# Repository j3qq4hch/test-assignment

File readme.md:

# SFP module

This repository contains source documentation for Gigabit SFP module based on RTL8211FS.
This is some sort of test assignment and not a real device.
The design is not tested in hardware (though looks fine in theory).

The design was done in EagleCAD. Any version starting from 7.7 should open the design just fine. 
3D model generated using NoABS.Eagle3d tool (not released yet).

The device looks like this:

3d model of the device is available [here](https://j3qq4hch.github.io/test-assignment/index.html?model=sfp.glb).

Schematic in pdf format can be found [here](sch.pdf).

One of the requirements of this test assignment was to find flaws in the design and fix them. Below is a list of these flaws:

* The overall schematic quality is poor.
* TXD+/TXD- on SFP connector side must be swapped.
* Ethernet connector has no embedded magnetics. Had to replace connector with [HanRun HR911130C](https://www.chipdip.ru/product/hr911130c-razyomy-i-soediniteli-hanrun-8048835943).
* The PCB is too narrow for the ethernet connector. It has to be a bit wider. 
* Some of the decoupling capacitors missing.
* Using proprietary and very expensive software for a test assignment likely assumes that the candidate will use pirated software, which is not a good practice.

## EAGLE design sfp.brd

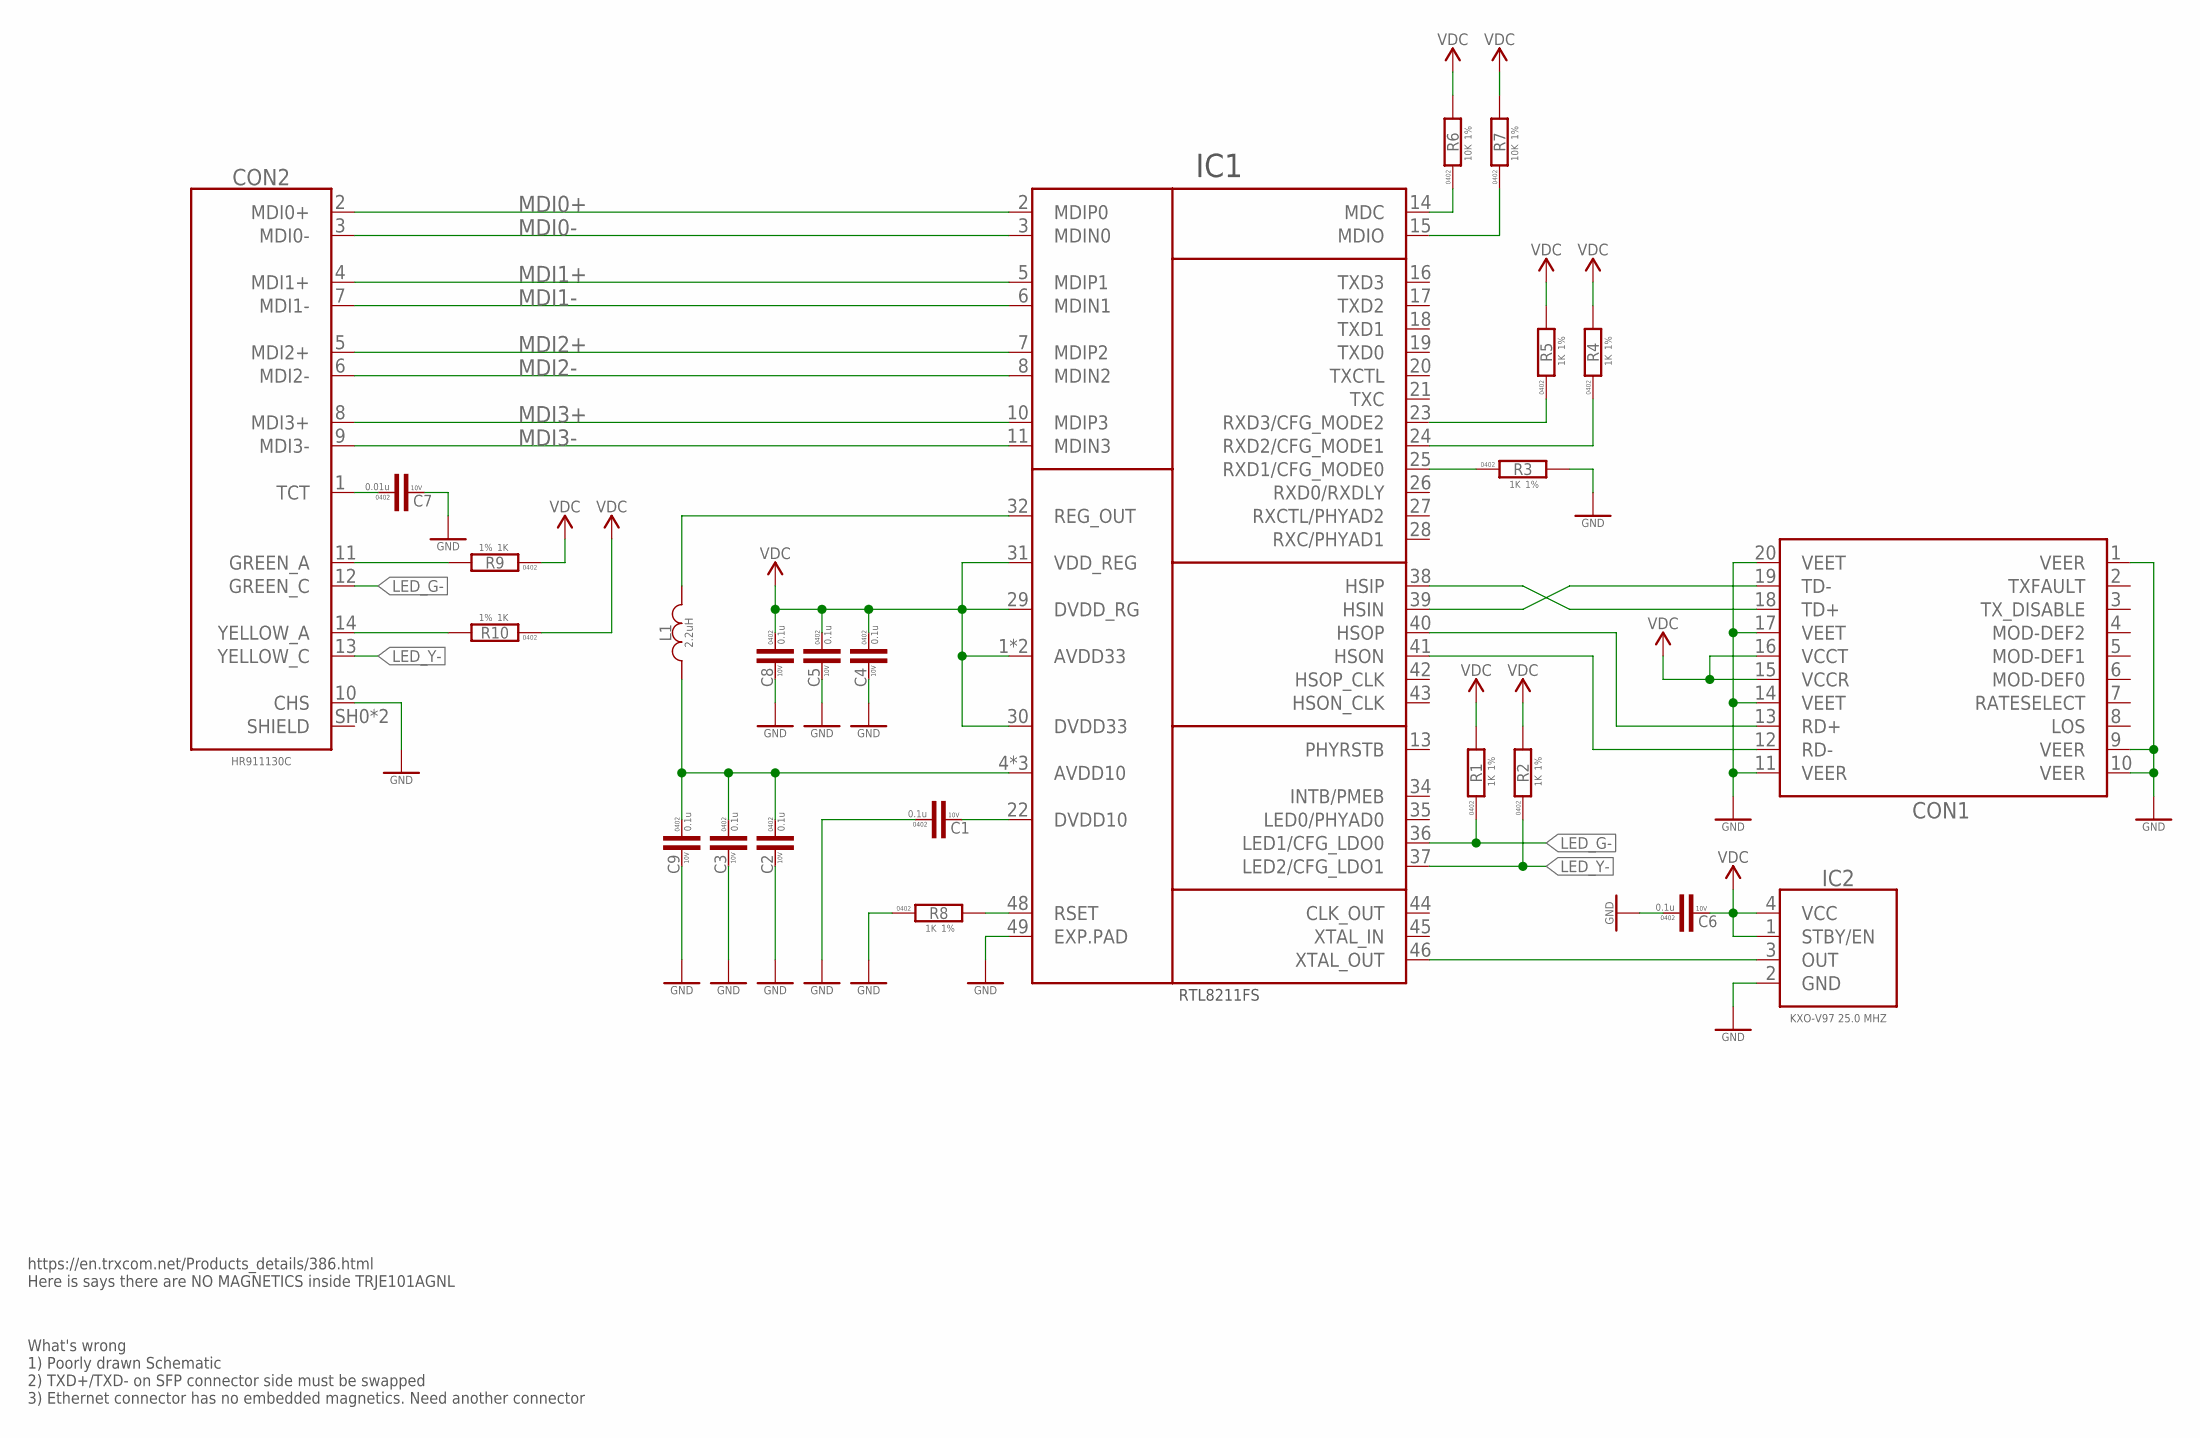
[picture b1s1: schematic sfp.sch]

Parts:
C1, C2, C3, C4, C5, C6, C8, C9: 0.1u; C0402; VOLTAGE 10V
C7: 0.01u; C0402; VOLTAGE 10V
CON1: SFA_EDGE_CON; SFP_EDGE_CON
CON2: HR911130C
IC1: RTL8211FS; QFN40
IC2: OSCILLATOR-KXO-V97; KXO-V97
L1: 2.2uH; L0805
R1, R2, R3, R4, R5, R8, R9, R10: 1K; R0402
R6, R7: 10K; R0402

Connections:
GND: C1.1, C2.2, C3.2, C4.2, C5.2, C6.1, C7.2, C8.2, C9.2, CON1.1 (VEER), CON1.9 (VEER), CON1.10 (VEER), CON1.11 (VEER), CON1.14 (VEET), CON1.17 (VEET), CON1.20 (VEET), CON2.10 (CHS), IC1.49 (EXP.PAD), IC2.2 (GND), R3.2, R8.1
LED_G-: CON2.12 (GREEN_C), IC1.36 (LED1/CFG_LDO0), R1.1
LED_Y-: CON2.13 (YELLOW_C), IC1.37 (LED2/CFG_LDO1), R2.1
MDI0+: CON2.2 (MDI0+), IC1.2 (MDIP0)
MDI0-: CON2.3 (MDI0-), IC1.3 (MDIN0)
MDI1+: CON2.4 (MDI1+), IC1.5 (MDIP1)
MDI1-: CON2.7 (MDI1-), IC1.6 (MDIN1)
MDI2+: CON2.5 (MDI2+), IC1.7 (MDIP2)
MDI2-: CON2.6 (MDI2-), IC1.8 (MDIN2)
MDI3+: CON2.8 (MDI3+), IC1.10 (MDIP3)
MDI3-: CON2.9 (MDI3-), IC1.11 (MDIN3)
unnamed: CON1.18 (TD+), IC1.38 (HSIP)
unnamed: CON1.19 (TD-), IC1.39 (HSIN)
unnamed: IC1.23 (RXD3/CFG_MODE2), R5.1
unnamed: IC1.24 (RXD2/CFG_MODE1), R4.1
unnamed: IC1.25 (RXD1/CFG_MODE0), R3.1
unnamed: IC1.14 (MDC), R6.1
unnamed: IC1.15 (MDIO), R7.1
unnamed: IC1.48 (RSET), R8.2
unnamed: C1.2, IC1.22 (DVDD10)
unnamed: IC1.32 (REG_OUT), L1.2
unnamed: C2.1, C3.1, C9.1, IC1.4 (AVDD10), IC1.9 (AVDD10), IC1.47 (AVDD10), L1.1
unnamed: C7.1, CON2.1 (TCT)
unnamed: CON1.13 (RD+), IC1.40 (HSOP)
unnamed: CON1.12 (RD-), IC1.41 (HSON)
unnamed: CON2.11 (GREEN_A), R9.2
unnamed: IC1.46 (XTAL_OUT), IC2.3 (OUT)
unnamed: CON2.14 (YELLOW_A), R10.2
VDC: C4.1, C5.1, C6.2, C8.1, CON1.15 (VCCR), CON1.16 (VCCT), IC1.1 (AVDD33), IC1.12 (AVDD33), IC1.29 (DVDD_RG), IC1.30 (DVDD33), IC1.31 (VDD_REG), IC2.1 (STBY/EN), IC2.4 (VCC), R1.2, R2.2, R4.2, R5.2, R6.2, R7.2, R9.1, R10.1

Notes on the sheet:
https://en.trxcom.net/Products_details/386.html Here is says there are NO MAGNETICS inside TRJE101AGNL
What's wrong 1) Poorly drawn Schematic 2) TXD+/TXD- on SFP connector side must be swapped 3) Ethernet connector has no embedded magnetics. Need another connector

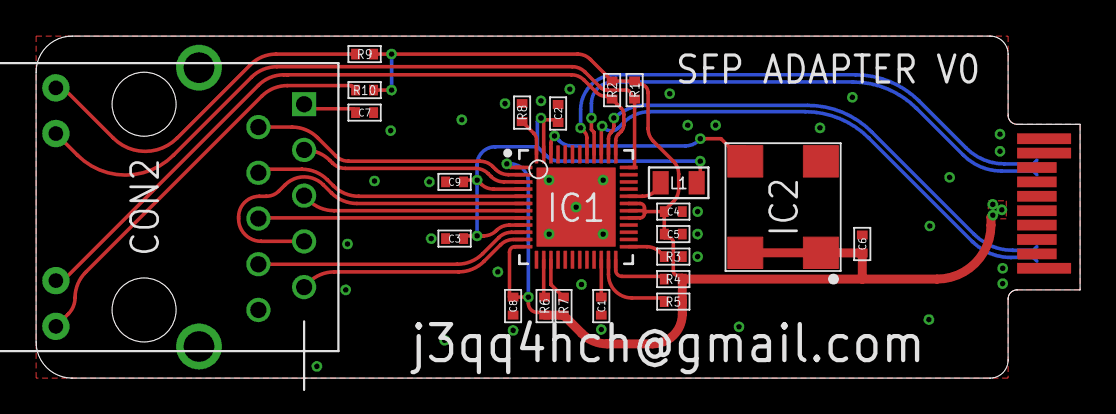
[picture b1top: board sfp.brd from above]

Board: 2 copper layers, 58.0 x 19.0 mm, 25 parts (1 on the bottom side), 29 nets.

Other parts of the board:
U$1: ART

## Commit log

2026-05-01 initial import
2026-05-01 some more import
2026-05-01 readme
